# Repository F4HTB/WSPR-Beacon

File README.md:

# WSPR-Beacon

This is a WSPR Beacon made with arduino, gps neo-7-m, lcd and SI5351 adafruit.
I use they library: SoftwareSerial, TinyGPS++, etherkit/si5351, and LiquidCrystal_I2C.

More infos on http://www.f4htb.fr/2018/01/02/balise-wspr-multibandes/

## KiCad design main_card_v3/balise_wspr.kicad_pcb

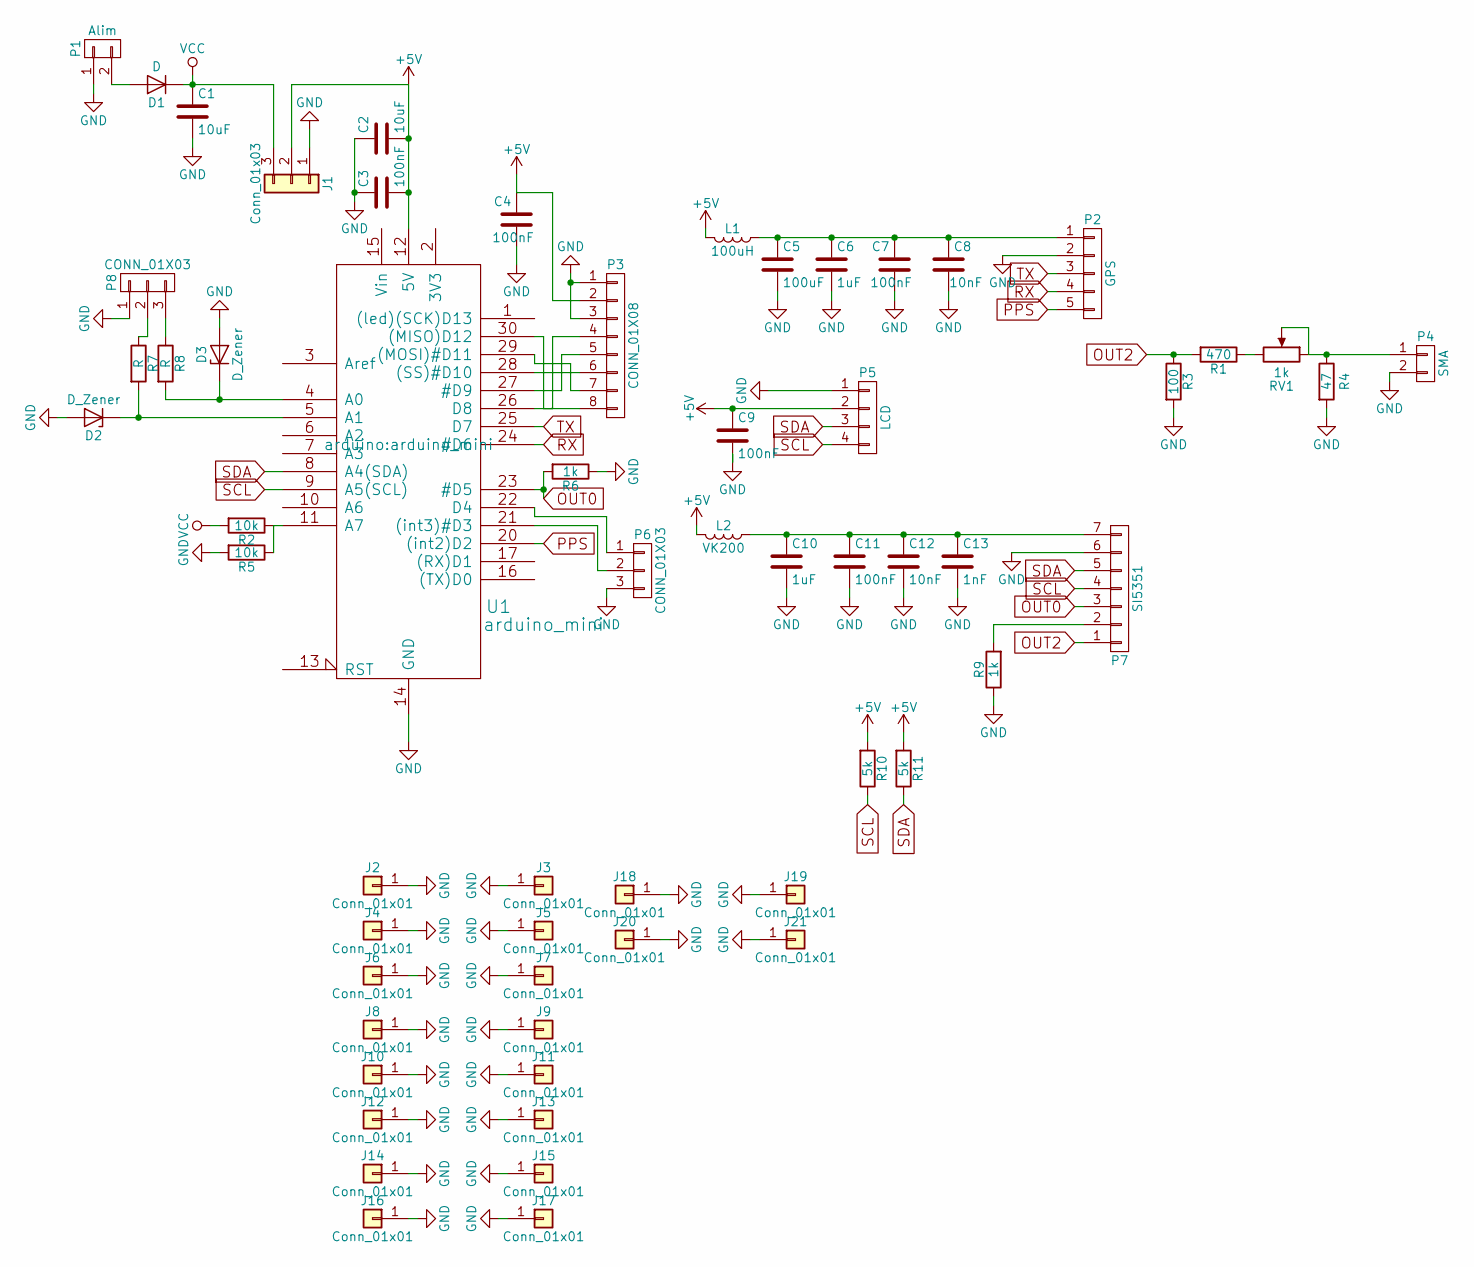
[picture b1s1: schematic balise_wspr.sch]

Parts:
C1, C2: 10uF; CP_Radial_D4.0mm_P1.50mm
C3, C4, C7, C9, C11: 100nF; C_0805_HandSoldering
C5: 100uF; CP_Radial_D10.0mm_P3.50mm
C6, C10: 1uF; CP_Radial_D4.0mm_P1.50mm
C8, C12: 10nF; C_0805_HandSoldering
C13: 1nF; C_0805_HandSoldering
D1: D; D_DO-41_SOD81_P7.62mm_Horizontal
D2, D3: D_Zener; R_Axial_DIN0207_L6.3mm_D2.5mm_P7.62mm_Horizontal
J1: Conn_01x03; TO-220_Horizontal
J2, J3, J4, J5, J6, J7, J8, J9, J10, J11, J12, J13, J14, J15, J16, J17, J18, J19, J20, J21: Conn_01x01; Pin_Header_Straight_1x01_Pitch2.54mm
L1: 100uH; CP_Radial_D10.0mm_P3.80mm
L2: VK200; Choke_Horizontal_RM15mm
P1: Alim; Molex_KK-41791-02_02x3.96mm_Straight
P2: GPS; Pin_Header_Straight_1x05_Pitch2.54mm
P3: CONN_01X08; Pin_Header_Straight_1x08_Pitch2.54mm
P4: SMA; sma_straight_32k101-400l5
P5: LCD; Pin_Header_Straight_1x04_Pitch2.54mm
P6, P8: CONN_01X03; Pin_Header_Straight_1x03_Pitch2.54mm
P7: SI5351; Pin_Header_Straight_1x07_Pitch2.54mm
R1: 470; R_0805_HandSoldering
R2, R5: 10k; R_Axial_DIN0207_L6.3mm_D2.5mm_P7.62mm_Horizontal
R3: 100; R_0805_HandSoldering
R4: 47; R_0805_HandSoldering
R6, R9: 1k; R_0805_HandSoldering
R7, R8: R; R_Axial_DIN0207_L6.3mm_D2.5mm_P7.62mm_Horizontal
R10, R11: 5k; R_0805_HandSoldering
RV1: 1k; Potentiometer_Trimmer_Bourns_3266Y
U1: arduino_mini

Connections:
+5V: C2.2, C3.2, C4.1, C9.1, J1.2, L1.2, L2.2, P3.2, P5.2, R10.2, R11.2, U1.12 (5V)
GND: C1.2, C2.1, C3.1, C4.2, C5.2, C6.2, C7.2, C8.2, C9.2, C10.2, C11.2, C12.2, C13.2, D2.2 (A), D3.2 (A), J1.1, J2.1, J3.1, J4.1, J5.1, J6.1, J7.1, J8.1, J9.1, J10.1, J11.1, J12.1, J13.1, J14.1, J15.1, J16.1, J17.1, J18.1, J19.1, J20.1, J21.1, P1.1, P2.2, P3.1, P3.3, P4.2, P5.1, P6.3, P7.6, P8.1, R3.2, R4.2, R5.2, R6.1, R9.1, U1.14 (GND), U1.19 (GND); also elsewhere on the board
unnamed 2: C5.1, C6.1, C7.1, C8.1, L1.1, P2.1; also elsewhere on the board
unnamed: C10.1, C11.1, C12.1, C13.1, L2.1, P7.7
unnamed: D1.2 (A), P1.2
unnamed: D2.1 (K), R7.2, U1.5 (A1)
unnamed: D3.1 (K), R8.2, U1.4 (A0)
unnamed: P3.4, U1.26 (D8)
unnamed: P3.5, U1.27 (#D9)
unnamed: P3.6, U1.28 ((SS)#D10)
unnamed: P3.7, U1.29 ((MOSI)#D11)
unnamed: P3.8, U1.30 ((MISO)D12)
unnamed: P4.1, R4.1, RV1.1, RV1.2
unnamed 13: P6.1, U1.22 (D4); also elsewhere on the board
unnamed 14: P6.2, U1.21 ((int3)#D3); also elsewhere on the board
unnamed: P7.2, R9.2
unnamed: P8.2, R7.1
unnamed: P8.3, R8.1
unnamed: R1.1, RV1.3
unnamed: R2.1, R5.1, U1.11 (A7)
OUT0: P7.3, R6.2, U1.23 (#D5)
OUT2: P7.1, R1.2, R3.1
PPS: P2.5, U1.20 ((int2)D2); also elsewhere on the board
RX: P2.4, U1.24 (#D6); also elsewhere on the board
SCL: P5.4, P7.4, R10.1, U1.9 (A5(SCL))
SDA: P5.3, P7.5, R11.1, U1.8 (A4(SDA))
TX: P2.3, U1.25 (D7); also elsewhere on the board
VCC: C1.1, D1.1 (K), J1.3, R2.2

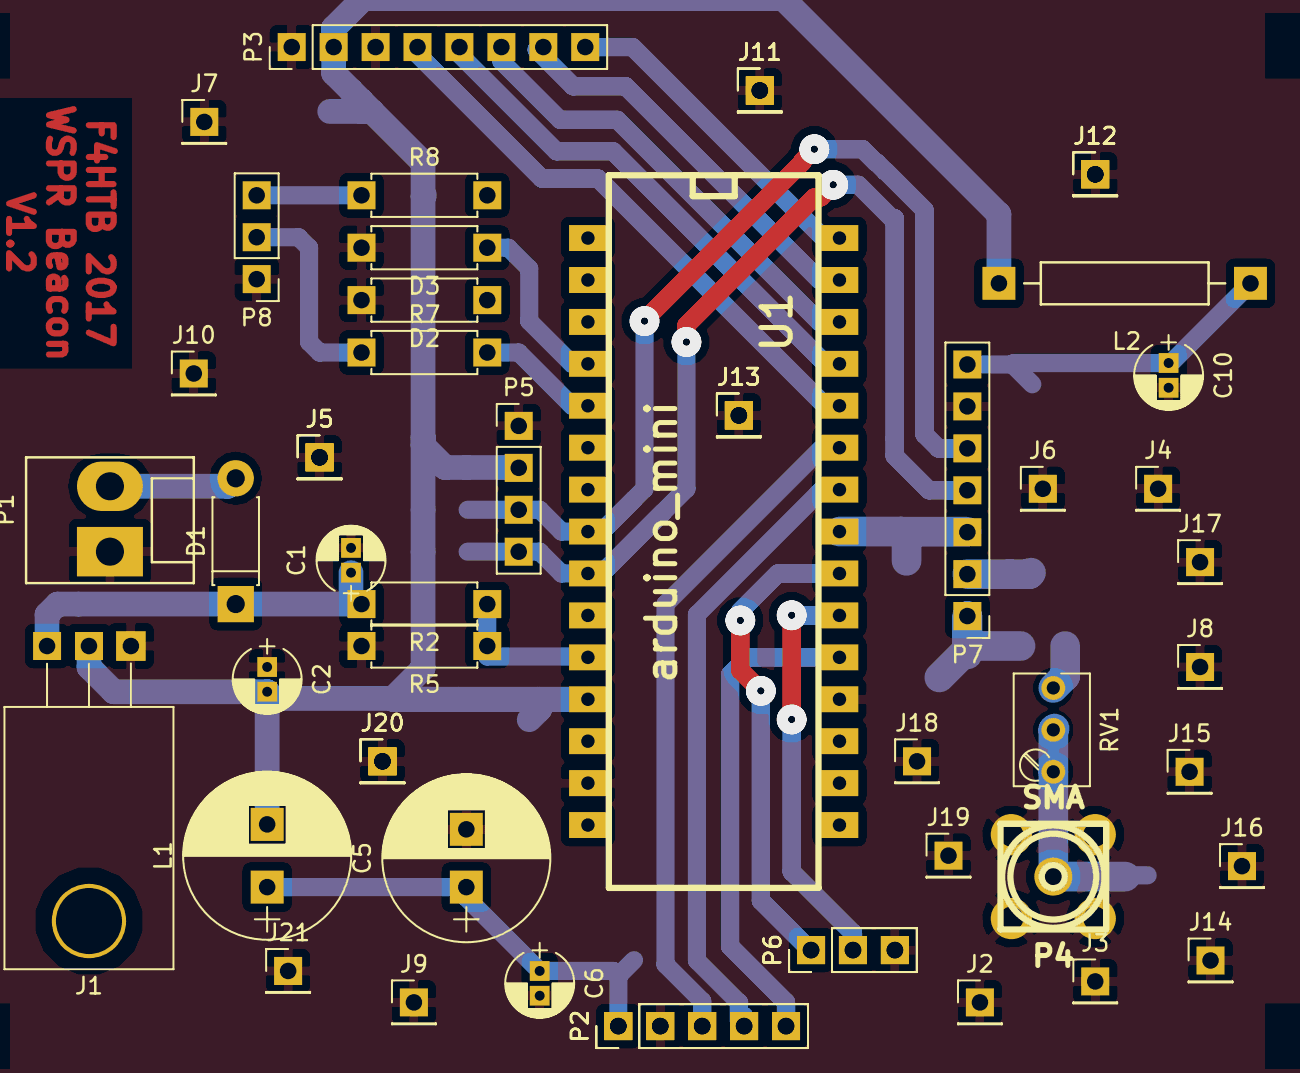
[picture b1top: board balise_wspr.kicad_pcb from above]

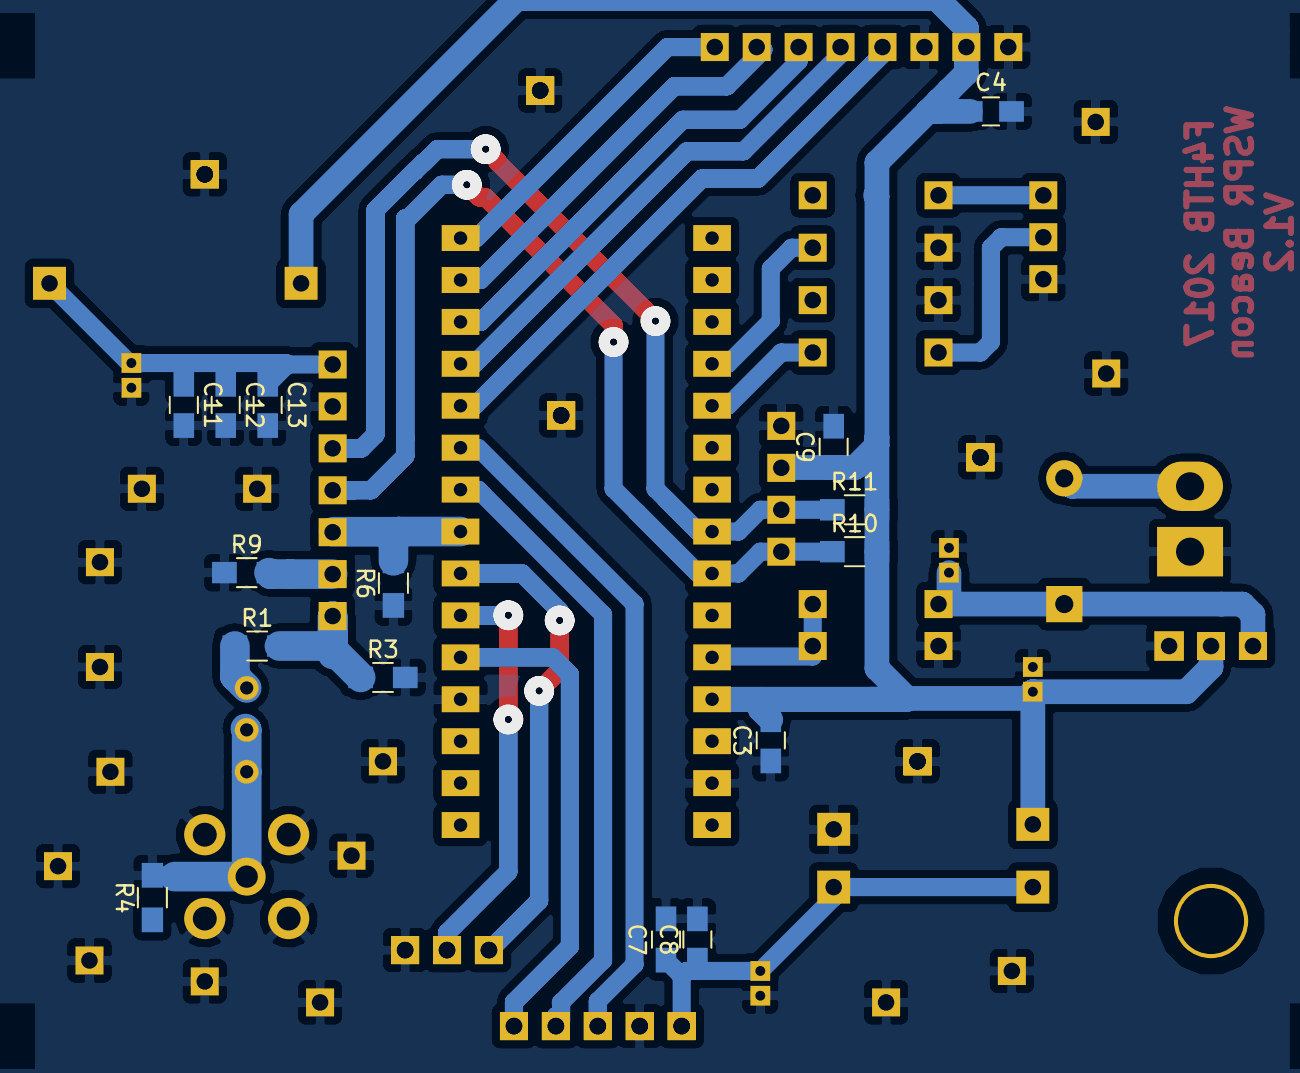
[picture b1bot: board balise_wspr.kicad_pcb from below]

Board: 2 copper layers, 67 parts (15 on the bottom side), 28 nets.

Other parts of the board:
J5#2, J11#2, J12#2, J13#2, J20#2: Conn_01x01; Pin_Header_Straight_1x01_Pitch2.54mm
P2#2: GPS; Pin_Header_Straight_1x05_Pitch2.54mm
P6#2: CONN_01X03; Pin_Header_Straight_1x03_Pitch2.54mm

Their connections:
GND: J5#2.1, J11#2.1, J12#2.1, J13#2.1, J20#2.1, P2#2.2, P6#2.3; also elsewhere on the board
unnamed 2: P2#2.1; also elsewhere on the board
unnamed 13: P6#2.1; also elsewhere on the board
unnamed 14: P6#2.2; also elsewhere on the board
PPS: P2#2.5; also elsewhere on the board
RX: P2#2.4; also elsewhere on the board
TX: P2#2.3; also elsewhere on the board
